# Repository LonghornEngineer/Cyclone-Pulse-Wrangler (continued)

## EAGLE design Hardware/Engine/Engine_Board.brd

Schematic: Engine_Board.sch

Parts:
3.3V: TEST_POINT_SINGLE_KEYSTONE_5115-5119; KEYSTONE_5115-5119
3.3V_PWR: MF-LED-0805-RED; LED_0805; MPN MF-LED-0805-RED
5V, 12V: TEST_POINT_SINGLE_KEYSTONE_5115-5119; KEYSTONE_5115-5119; MPN 5115
C1, C2, C3, C4, C7, C8, C9, C11, C12, C25, C26, C31, C32, C33, C34, C35, C37, C38, C39, C40: 0.1uF; 0805
C5: 0.1uF; 0603
C6, C44, C45: 10uF; 1210
C10, C13, C29, C30: 4.7uF; 1210; MPN GRJ32DC72A475KE11L
C14: 1uf; 0805; MPN C0805C105K5RACTU
C15: 1000uF; 10MM_CAP_SMD; MPN UWZ1A102MCL1GS
C16, C23: 0.1uF; 0805; MPN MF-CAP-0805-0.1uF
C17: 10uF; 1206; MPN MF-CAP-1206-10uF
C18: 1000uF; 12.5MM_CAP_PTH; MPN UBW1H102MHD
C19: 220uF; 10MM_CAP_SMD; MPN UWZ1H221MCL1GS
C22: 10uF; 1210; MPN MF-CAP-1206-10uF
C24: 47uF; 6.3MM_CAP_SMD; MPN UWJ1C470MCL1GB
C27: 0.01uF; 0805; MPN C0805C103K5RACTU
C28: 180uF; 8MM_CAP_SMD; MPN 16SVP180M
C36: 4.7uF; 0805
C41, C42, C43: .1uF; 0603
D2: VS-12CWQ10FN-M3; D-PAK(TO-252AA); MPN VS-12CWQ10FN-M3
D3: VB20100S-E3/8W; D2PAK(TO-263AB)
D7, D8, D9, D10: NUP2105LT1G; SOT-23
DISP1: 61201621621; CU40045-UW1J
FID1, FID2: FIDUCIAL_0.5MM
GND: TEST_POINT_SINGLE_KEYSTONE_5115-5119; KEYSTONE_5115-5119; MPN 5115
J1, J2, J3, J4, J5: CON_01X02_1546215-2; 1546215-2
J6: 3PCV-03-006; MPN 3PCV-03-006
L3: 6.8uH; IHLP-5050; MPN IHLP5050CEER6R8M01
PROP_TC: TC2030-NL; TC2030
PROP_UART: CON_01X06_2.54MM_PIN_HEADER; 2.54MM_01X06_PIN_HEADER
R1, R9, R10, R15, R16, R17: 10K; 0805
R2: 470K; 0603; MPN MF-RES-0603-470K
R3, R4, R5, R6, R7, R8, R14, R18: 120; 0603
R11: 330; 0603; MPN MF-RES-0603-330
R12, R13: 10K; 0603
R19, R20, R21, R22, R23, R24, R25, R26, R27, R28, R29, R30, R31, R32, R33, R34, R35, R36, R37, R38, R39, R40, R41, R42, R43, R44, R45: RESISTOR_0603; R0603
RELAYS: CON_01X10_1-282834-0; 1-282834-0
SW1, SW2, SW3: MF-SW-TACT-4.2MM; TACT4.2MM
SWITCHS: CON_01X10_1-282834-0; 1-282834-0
SW_D: CON_01X02_1546215-2; 1546215-2
SW_S: CON_01X02_1546215-2; 1546215-2
SW_U: CON_01X02_1546215-2; 1546215-2
TVS1: V18AUMLA2220H; 2220
U1: P8X32A-Q44; LQFP44
U2, U3, U8, U12, U13, U15, U17, U18, U19, U20, U21, U22, U23, U24, U25, U26: G3VM-61GR2(TR05); G3VM-61GR2
U4, U9, U10, U11: MAX31855KASA+; MAX31855_SO-8
U5: LM22678TJ-5.0/NOPB; LM22678_TO-263-EP-7; MPN LM22678TJ-5.0/NOPB
U6: ADP3338AKCZ-3.3-RL; ADP3338_SOT-223-3; MPN ADP3338AKCZ-3.3-RL
U7: CAT24C512WI-GT3; SOIC-8_W
U14: CD74HC595M96; CD74HC595_SOIC-16
U16: CD74HC165M96; CD74HC165_SOIC-16
U27: FXOS8700CQR1
U28: ACPL-C870-000E; ACPL-C87_SSO-8
U29: MAX11613EUA+; MAX11613_UMAX-8
U30: TPS7B6933QDCYRQ1; SOT-23-5
U$1: LHE_FRAME
U$35: JEEP_LOGO_SILK_MEDIUM; JEEP_SILK_MEDIUM
U$42: LHE_LOGOLHE_LOGO; LHE_LOGO
X1: ABMM-6.000MHZ-B2-T; 7MMX5MM

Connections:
3.3V: 3.3V.P$1, C1.1, C2.1, C3.1, C4.1, C7.1, C8.1, C9.1, C11.1, C22.1, C23.1, C24.POS, C25.1, C31.1, C32.1, C34.1, C36.1, C37.1, C38.1, C41.1, C43.1, R1.2, R9.1, R10.1, R11.1, R12.2, R13.2, R15.2, R16.2, R17.1, R28.P$2, R29.P$2, R30.P$2, R31.P$2, R32.P$2, R33.P$2, R34.P$2, R35.P$2, U1.8 (VDD), U1.18 (VDD), U1.30 (VDD), U1.40 (VDD), U4.4 (VCC), U6.2 (OUT), U6.PAD (OUT), U7.8 (VCC), U9.4 (VCC), U10.4 (VCC), U11.4 (VCC), U14.10 (MR), U14.16 (VCC), U16.16 (VCC), U27.P$1 (VDDIO), U27.P$14 (VDD), U28.P$8 (VDD2), U29.P$8 (VCC)
5V: 5V.P$1, C13.1, C15.POS, C16.1, C17.1, C28.POS, L3.1, U5.P$6 (FB), U6.3 (IN)
5V_PWR: C6.1, DISP1.P$13 (VCC)
12V: 12V.P$1, C10.1, C14.1, C18.POS, C19.POS, C29.1, C30.1, D2.PAD-4 (CATHODE), R2.1, U5.P$2 (VIN)
12V_BATT: D2.1 (ANODE), D2.3 (ANODE), J6.1 (PIN1), TVS1.P$2
12V_BATT_ON: C44.1, U30.P$1 (VIN)
165_CLK: U1.14 (P13), U16.2 (CLK)
165_DATA: U1.12 (P11), U16.9 (QH)
165_LOAD: U1.13 (P12), U16.1 (LAT)
595_CLK: U1.19 (P16), U14.11 (SHCP)
595_DATA: U1.15 (P14), U14.14 (DS)
595_LAT: U1.16 (P15), U14.12 (STCP)
!RES!_PROP: C5.1, PROP_TC.P$6 (PIN6), PROP_UART.6
A0: R43.P$2, U29.P$1 (A_0)
A1: U29.P$2 (A_1)
A2: U29.P$3 (A_2)
A3: U29.P$4 (A_3)
CHASSIS_GND: C44.2, C45.2, R44.P$1, U2.P$3 (3), U3.P$3 (3), U8.P$3 (3), U12.P$3 (3), U13.P$3 (3), U15.P$3 (3), U17.P$3 (3), U18.P$3 (3), U19.P$2 (CATHODE), U20.P$2 (CATHODE), U21.P$2 (CATHODE), U22.P$2 (CATHODE), U23.P$2 (CATHODE), U24.P$2 (CATHODE), U25.P$2 (CATHODE), U26.P$2 (CATHODE), U28.P$3 (SHDN), U28.P$4 (GND1), U30.P$3 (GND/ADJ), U30.P$4 (GND/ADJ)
D4: DISP1.P$3 (D4), R6.2
D5: DISP1.P$4 (D5), R5.2
D6: DISP1.P$1 (D6), R4.2
D7: DISP1.P$2 (D7), R3.2
DOME_PWR: J6.3 (PIN3)
E1: DISP1.P$10 (E1), R8.2
E2: DISP1.P$16 (E2), R7.2
EXT_5V: C45.1, U28.P$1 (VDD1), U30.P$5 (VOUT)
GND: 3.3V_PWR.CATHODE, C1.2, C2.2, C3.2, C4.2, C6.2, C7.2, C8.2, C9.2, C10.2, C11.2, C13.2, C14.2, C15.NEG, C16.2, C17.2, C18.NEG, C19.NEG, C22.2, C23.2, C24.NEG, C25.2, C26.2, C28.NEG, C29.2, C30.2, C31.2, C32.2, C34.2, C36.2, C37.2, C38.2, C40.2, C41.2, C42.2, C43.2, D3.A (ANODE), D7.3, D8.3, D9.3, D10.3, DISP1.P$5 (D2), DISP1.P$6 (D3), DISP1.P$7 (D0), DISP1.P$8 (D1), DISP1.P$14 (GND), GND.P$1, J6.2 (PIN2), PROP_TC.P$5 (PIN5), PROP_UART.1, SW1.P$4, SW2.P$4, SW3.P$4, SW_D.P$2 (PIN2), SW_S.P$2 (PIN2), SW_U.P$2 (PIN2), TVS1.P$1, U1.5 (VSS), U1.6 (BOE'), U1.17 (VSS), U1.27 (VSS), U1.39 (VSS), U2.P$2 (CATHODE), U3.P$2 (CATHODE), U4.1 (GND), U5.P$4 (GND), U5.PAD (GND), U6.1 (GND), U7.2 (A1), U7.3 (A2), U7.4 (GND), U7.7 (WP), U8.P$2 (CATHODE), U9.1 (GND), U10.1 (GND), U11.1 (GND), U12.P$2 (CATHODE), U13.P$2 (CATHODE), U14.8 (GND), U14.13 (OE), U15.P$2 (CATHODE), U16.8 (GND), U16.15 (C_INH), U17.P$2 (CATHODE), U18.P$2 (CATHODE), U19.P$3 (3), U20.P$3 (3), U21.P$3 (3), U22.P$3 (3), U23.P$3 (3), U24.P$3 (3), U25.P$3 (3), U26.P$3 (3), U27.P$3 (GND), U27.P$5 (GND), U27.P$7 (SA0/MISO), U27.P$10 (SA1/CS_B), U27.P$12 (GND), U27.P$13 (GND), U27.P$16 (RST), U28.P$5 (GND2), U28.P$6 (VOUT-), U29.P$7 (GND), X1.P$2 (GND), X1.P$4 (GND)
IN_OPTO_1: R29.P$1, U16.12 (D1), U20.P$4 (4)
IN_OPTO_2: R30.P$1, U16.13 (D2), U21.P$4 (4)
IN_OPTO_3: R31.P$1, U16.14 (D3), U22.P$4 (4)
IN_OPTO_4: R32.P$1, U16.3 (D4), U23.P$4 (4)
IN_OPTO_5: R33.P$1, U16.4 (D5), U24.P$4 (4)
IN_OPTO_6: R34.P$1, U16.5 (D6), U25.P$4 (4)
IN_OPTO_7: R35.P$1, U16.6 (D7), U26.P$4 (4)
unnamed: R28.P$1, U16.11 (D0), U19.P$4 (4)
unnamed: C27.1, U5.P$3 (BOOT)
unnamed: R27.P$1, U19.P$1 (ANODE)
unnamed: R36.P$1, U20.P$1 (ANODE)
unnamed: C27.2, D3.C (CATHODE), L3.2, U5.P$1 (SW)
unnamed: R37.P$1, U21.P$1 (ANODE)
unnamed: C26.1, U27.P$2 (BYP)
unnamed: C40.1, U27.P$8 (CRST)
unnamed: 3.3V_PWR.ANODE, R11.2
unnamed: R38.P$1, U22.P$1 (ANODE)
unnamed: R19.P$2, U2.P$1 (ANODE)
unnamed: R20.P$2, U3.P$1 (ANODE)
unnamed: R21.P$2, U8.P$1 (ANODE)
unnamed: R22.P$2, U12.P$1 (ANODE)
unnamed: R23.P$2, U13.P$1 (ANODE)
unnamed: R24.P$2, U15.P$1 (ANODE)
unnamed: R25.P$2, U17.P$1 (ANODE)
unnamed: R26.P$2, U18.P$1 (ANODE)
unnamed: R39.P$1, U23.P$1 (ANODE)
unnamed: R40.P$1, U24.P$1 (ANODE)
unnamed: R41.P$1, U25.P$1 (ANODE)
unnamed: R42.P$1, U26.P$1 (ANODE)
unnamed: R27.P$2, SWITCHS.P$1 (1)
unnamed: R36.P$2, SWITCHS.P$2 (2)
unnamed: R37.P$2, SWITCHS.P$3 (3)
unnamed: R38.P$2, SWITCHS.P$4 (4)
unnamed: R39.P$2, SWITCHS.P$5 (5)
unnamed: R40.P$2, SWITCHS.P$6 (6)
unnamed: R41.P$2, SWITCHS.P$7 (7)
unnamed: R42.P$2, SWITCHS.P$8 (8)
unnamed: R2.2, U5.P$7 (EN)
unnamed: C42.1, R43.P$1, U28.P$7 (VOUT+)
unnamed: R44.P$2, R45.P$2, U28.P$2 (VIN)
unnamed: J5.P$1 (PIN1), R45.P$1
OUT_0: R19.P$1, U14.15 (Q0)
OUT_1: R20.P$1, U14.1 (Q1)
OUT_2: R21.P$1, U14.2 (Q2)
OUT_3: R22.P$1, U14.3 (Q3)
OUT_4: R23.P$1, U14.4 (Q4)
OUT_5: R24.P$1, U14.5 (Q5)
OUT_6: R25.P$1, U14.6 (Q6)
OUT_7: R26.P$1, U14.7 (Q7)
P0: U1.41 (P0)
P17: U1.20 (P17)
P18: U1.21 (P18)
PROP_D4: R6.1, U1.44 (P3)
PROP_D5: R5.1, U1.1 (P4)
PROP_D6: R4.1, U1.42 (P1)
PROP_D7: R3.1, U1.43 (P2)
PROP_E1: R8.1, U1.2 (P5)
PROP_E2: R7.1, U1.9 (P8)
PROP_R/W: R14.1, U1.3 (P6)
PROP_RES: C5.2, R1.1, U1.7 (RES')
PROP_RS: R18.1, U1.4 (P7)
R/W: DISP1.P$9 (R/W), R14.2
RLY_0: RELAYS.P$1 (1), U2.P$4 (4)
RLY_1: RELAYS.P$2 (2), U3.P$4 (4)
RLY_2: RELAYS.P$3 (3), U8.P$4 (4)
RLY_3: RELAYS.P$4 (4), U12.P$4 (4)
RLY_4: RELAYS.P$5 (5), U13.P$4 (4)
RLY_5: RELAYS.P$6 (6), U15.P$4 (4)
RLY_6: RELAYS.P$7 (7), U17.P$4 (4)
RLY_7: RELAYS.P$8 (8), U18.P$4 (4)
RS: DISP1.P$12 (RS), R18.2
RX_PROP: PROP_TC.P$4 (PIN4), PROP_UART.4, U1.38 (P31)
SCL: R15.1, U1.35 (P28), U7.6 (SCL)
SCL_1: R12.1, U1.11 (P10), U27.P$4 (SCL/SCKL), U29.P$5 (SCL)
SDA: R16.1, U1.36 (P29), U7.5 (SDA)
SDA_1: R13.1, U1.10 (P9), U27.P$6 (SDA/MOSI), U29.P$6 (SDA)
SW_D: R9.2, SW3.P$1, SW_D.P$1 (PIN1), U1.22 (P19)
SW_S: R10.2, SW2.P$1, SW_S.P$1 (PIN1), U1.23 (P20)
SW_U: R17.2, SW1.P$1, SW_U.P$1 (PIN1), U1.24 (P21)
T+_0: C33.1, D8.1, J1.P$1 (PIN1), U9.3 (T+)
T+_1: C35.1, D9.1, J2.P$1 (PIN1), U10.3 (T+)
T+_2: C39.1, D7.1, J3.P$1 (PIN1), U11.3 (T+)
T+_3: C12.1, D10.1, J4.P$1 (PIN1), U4.3 (T+)
T-_0: C33.2, D8.2, J1.P$2 (PIN2), U9.2 (T-)
T-_1: C35.2, D9.2, J2.P$2 (PIN2), U10.2 (T-)
T-_2: C39.2, D7.2, J3.P$2 (PIN2), U11.2 (T-)
T-_3: C12.2, D10.2, J4.P$2 (PIN2), U4.2 (T-)
TC_CS_0: U1.25 (P22), U9.6 (!CS)
TC_CS_1: U1.26 (P23), U10.6 (!CS)
TC_CS_2: U1.31 (P24), U11.6 (!CS)
TC_CS_3: U1.32 (P25), U4.6 (!CS)
TC_SCK: U1.34 (P27), U4.5 (SCK), U9.5 (SCK), U10.5 (SCK), U11.5 (SCK)
TC_SO: U1.33 (P26), U4.7 (SO), U9.7 (SO), U10.7 (SO), U11.7 (SO)
TX_PROP: PROP_TC.P$3 (PIN3), PROP_UART.5, U1.37 (P30)
X0: U1.29 (X0), X1.P$1 (X0)
X1: U1.28 (X1), X1.P$3 (X1)

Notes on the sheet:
POWER INPUT
5V POWER SUPPLY

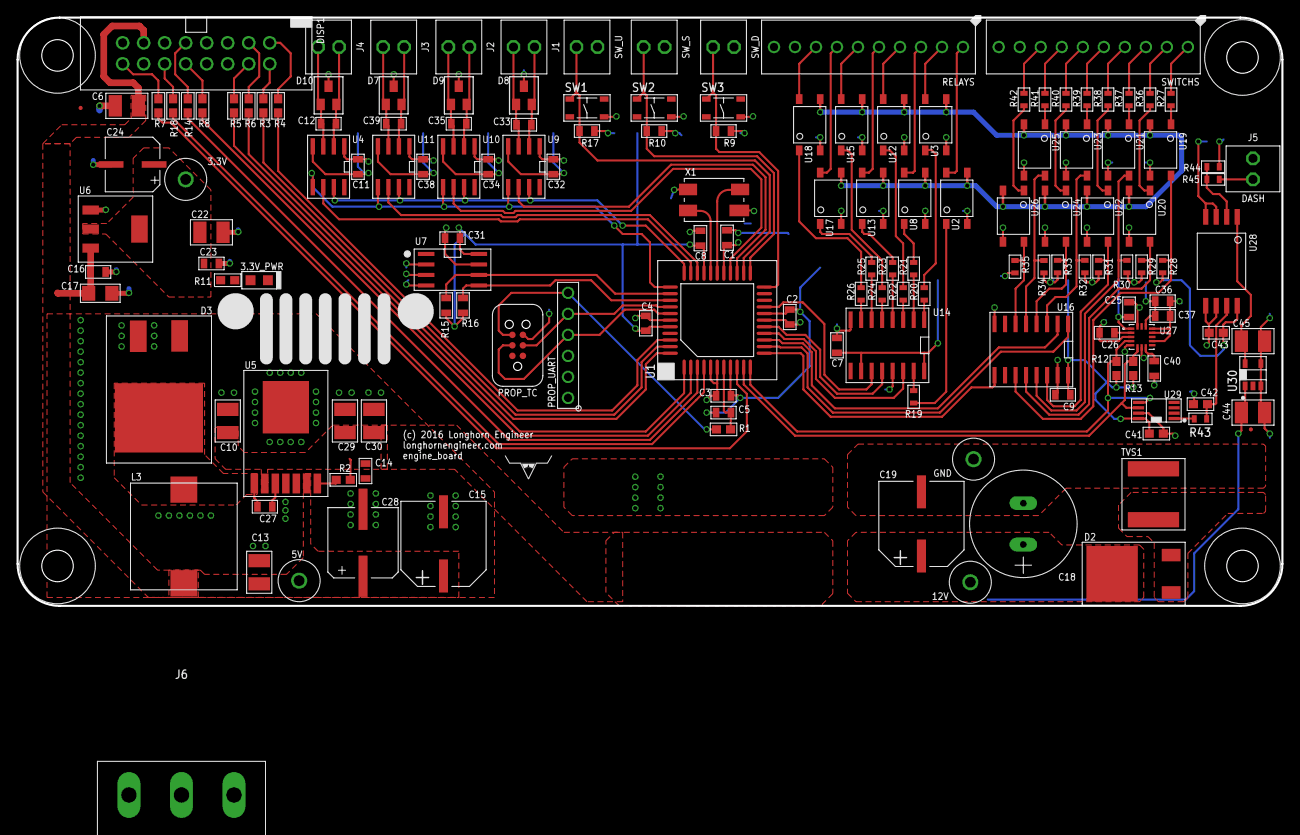
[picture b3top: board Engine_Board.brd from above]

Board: 2 copper layers, 152.9 x 71.1 mm, 158 parts (0 on the bottom side), 116 nets.

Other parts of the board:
U$31, U$32, U$33, U$34: MOUNT_HOLE_150MIL

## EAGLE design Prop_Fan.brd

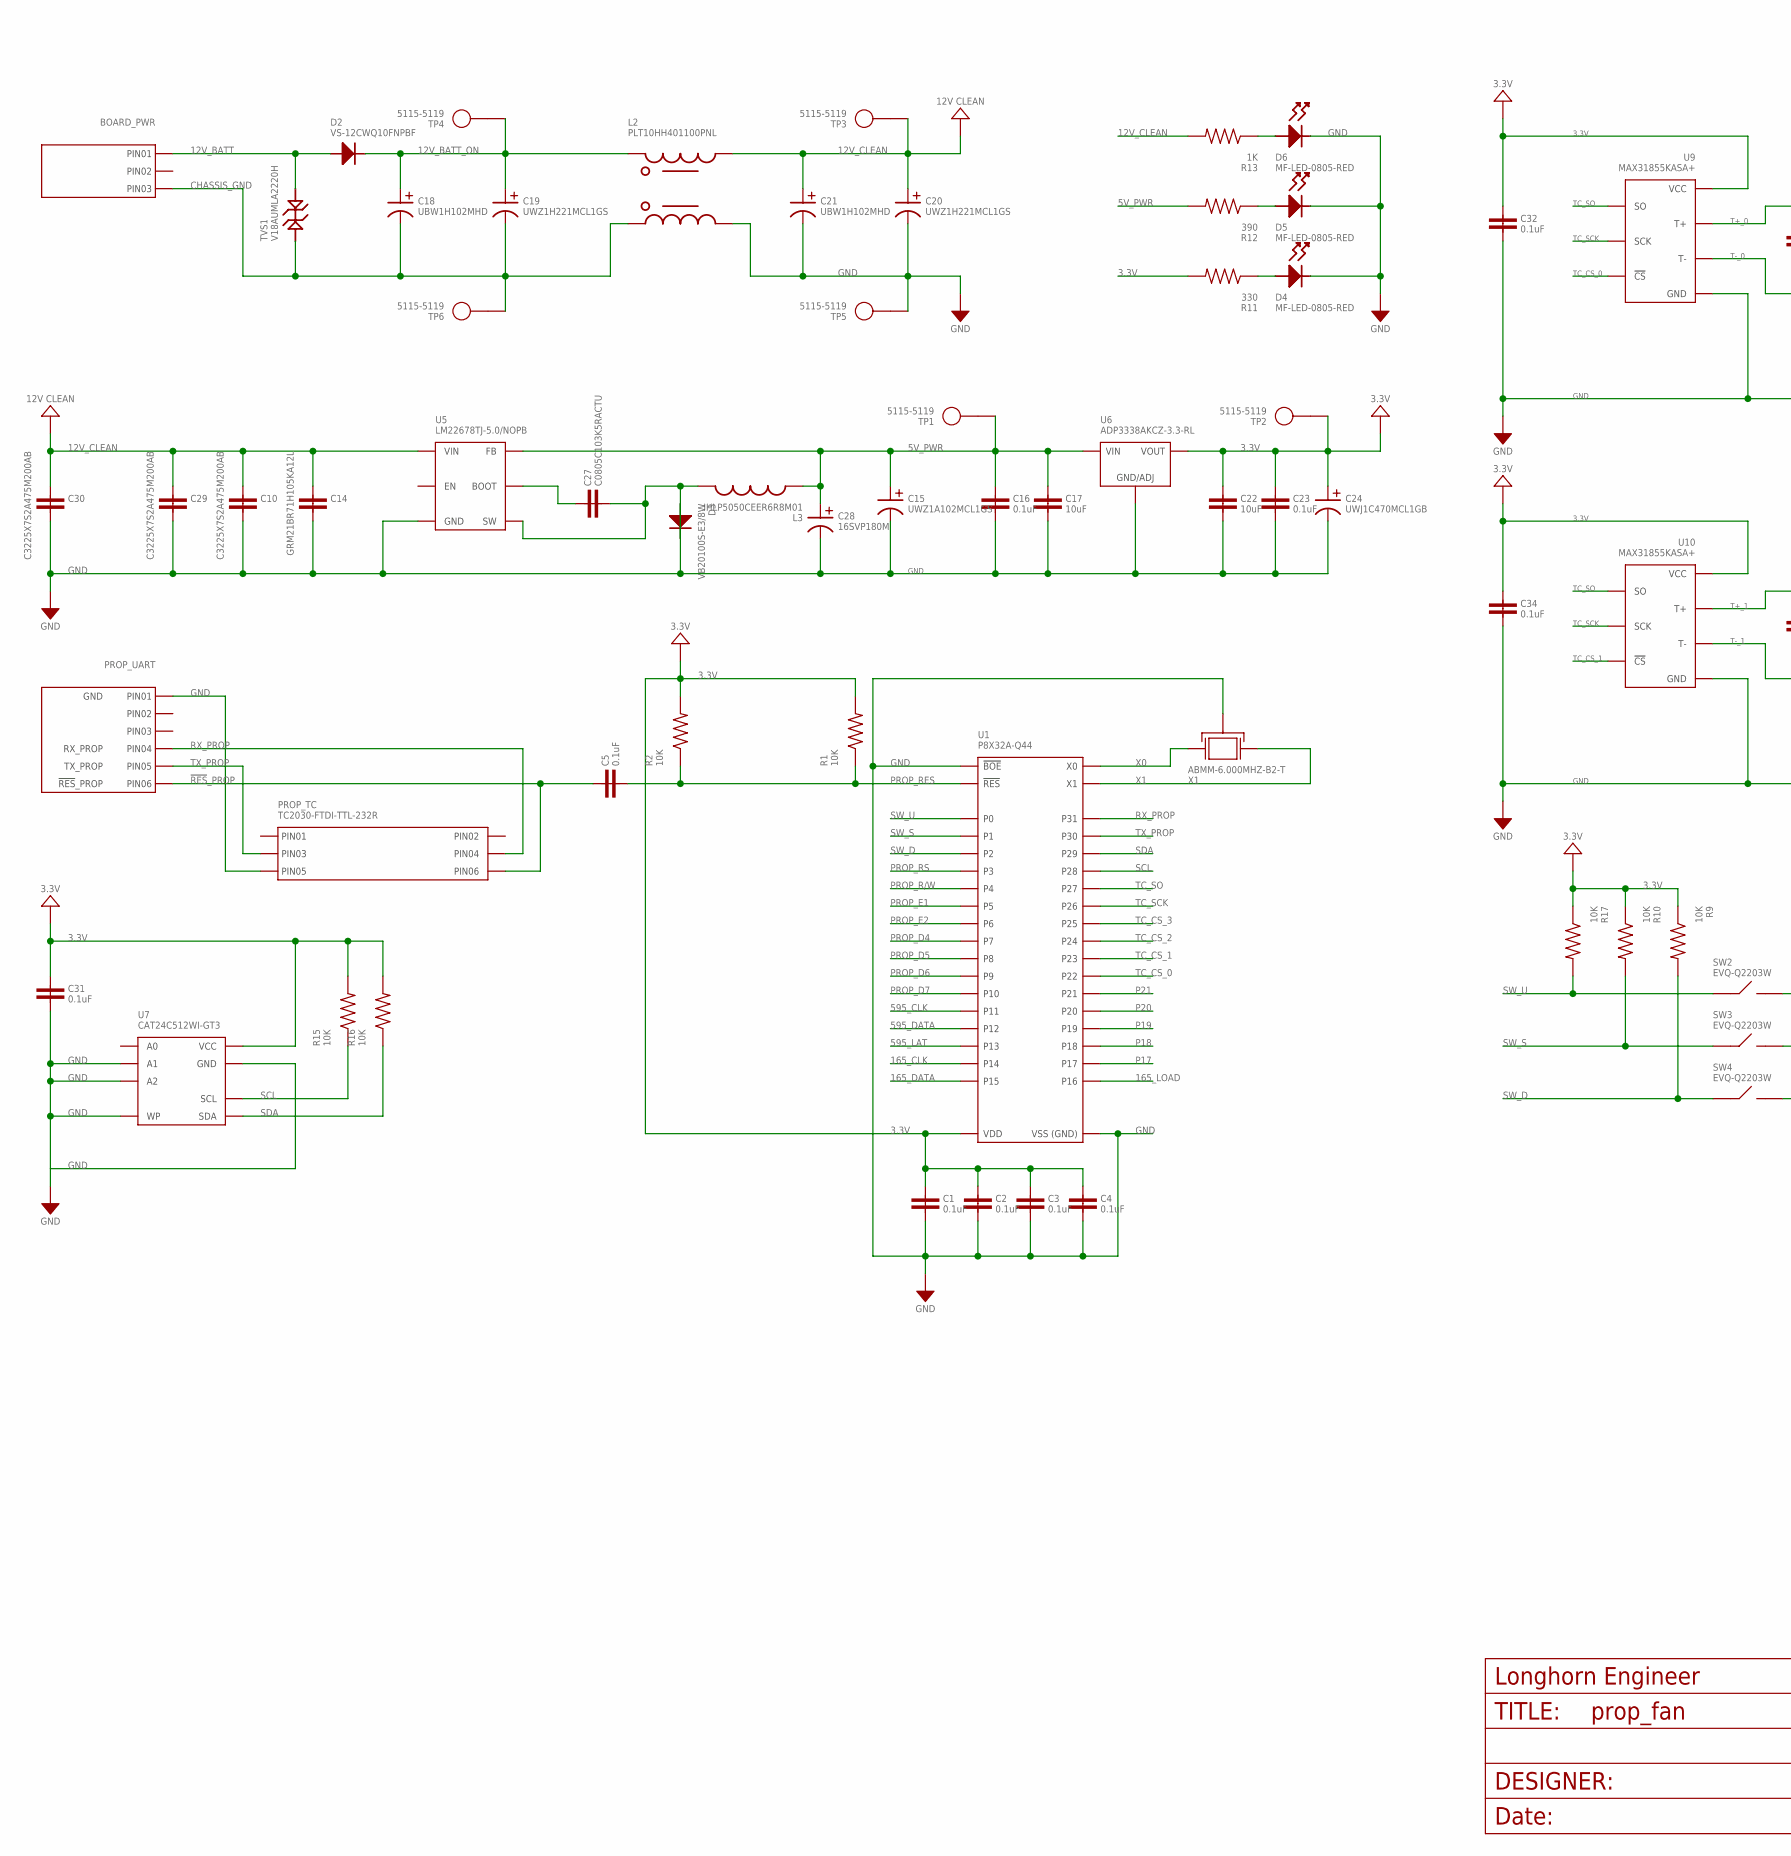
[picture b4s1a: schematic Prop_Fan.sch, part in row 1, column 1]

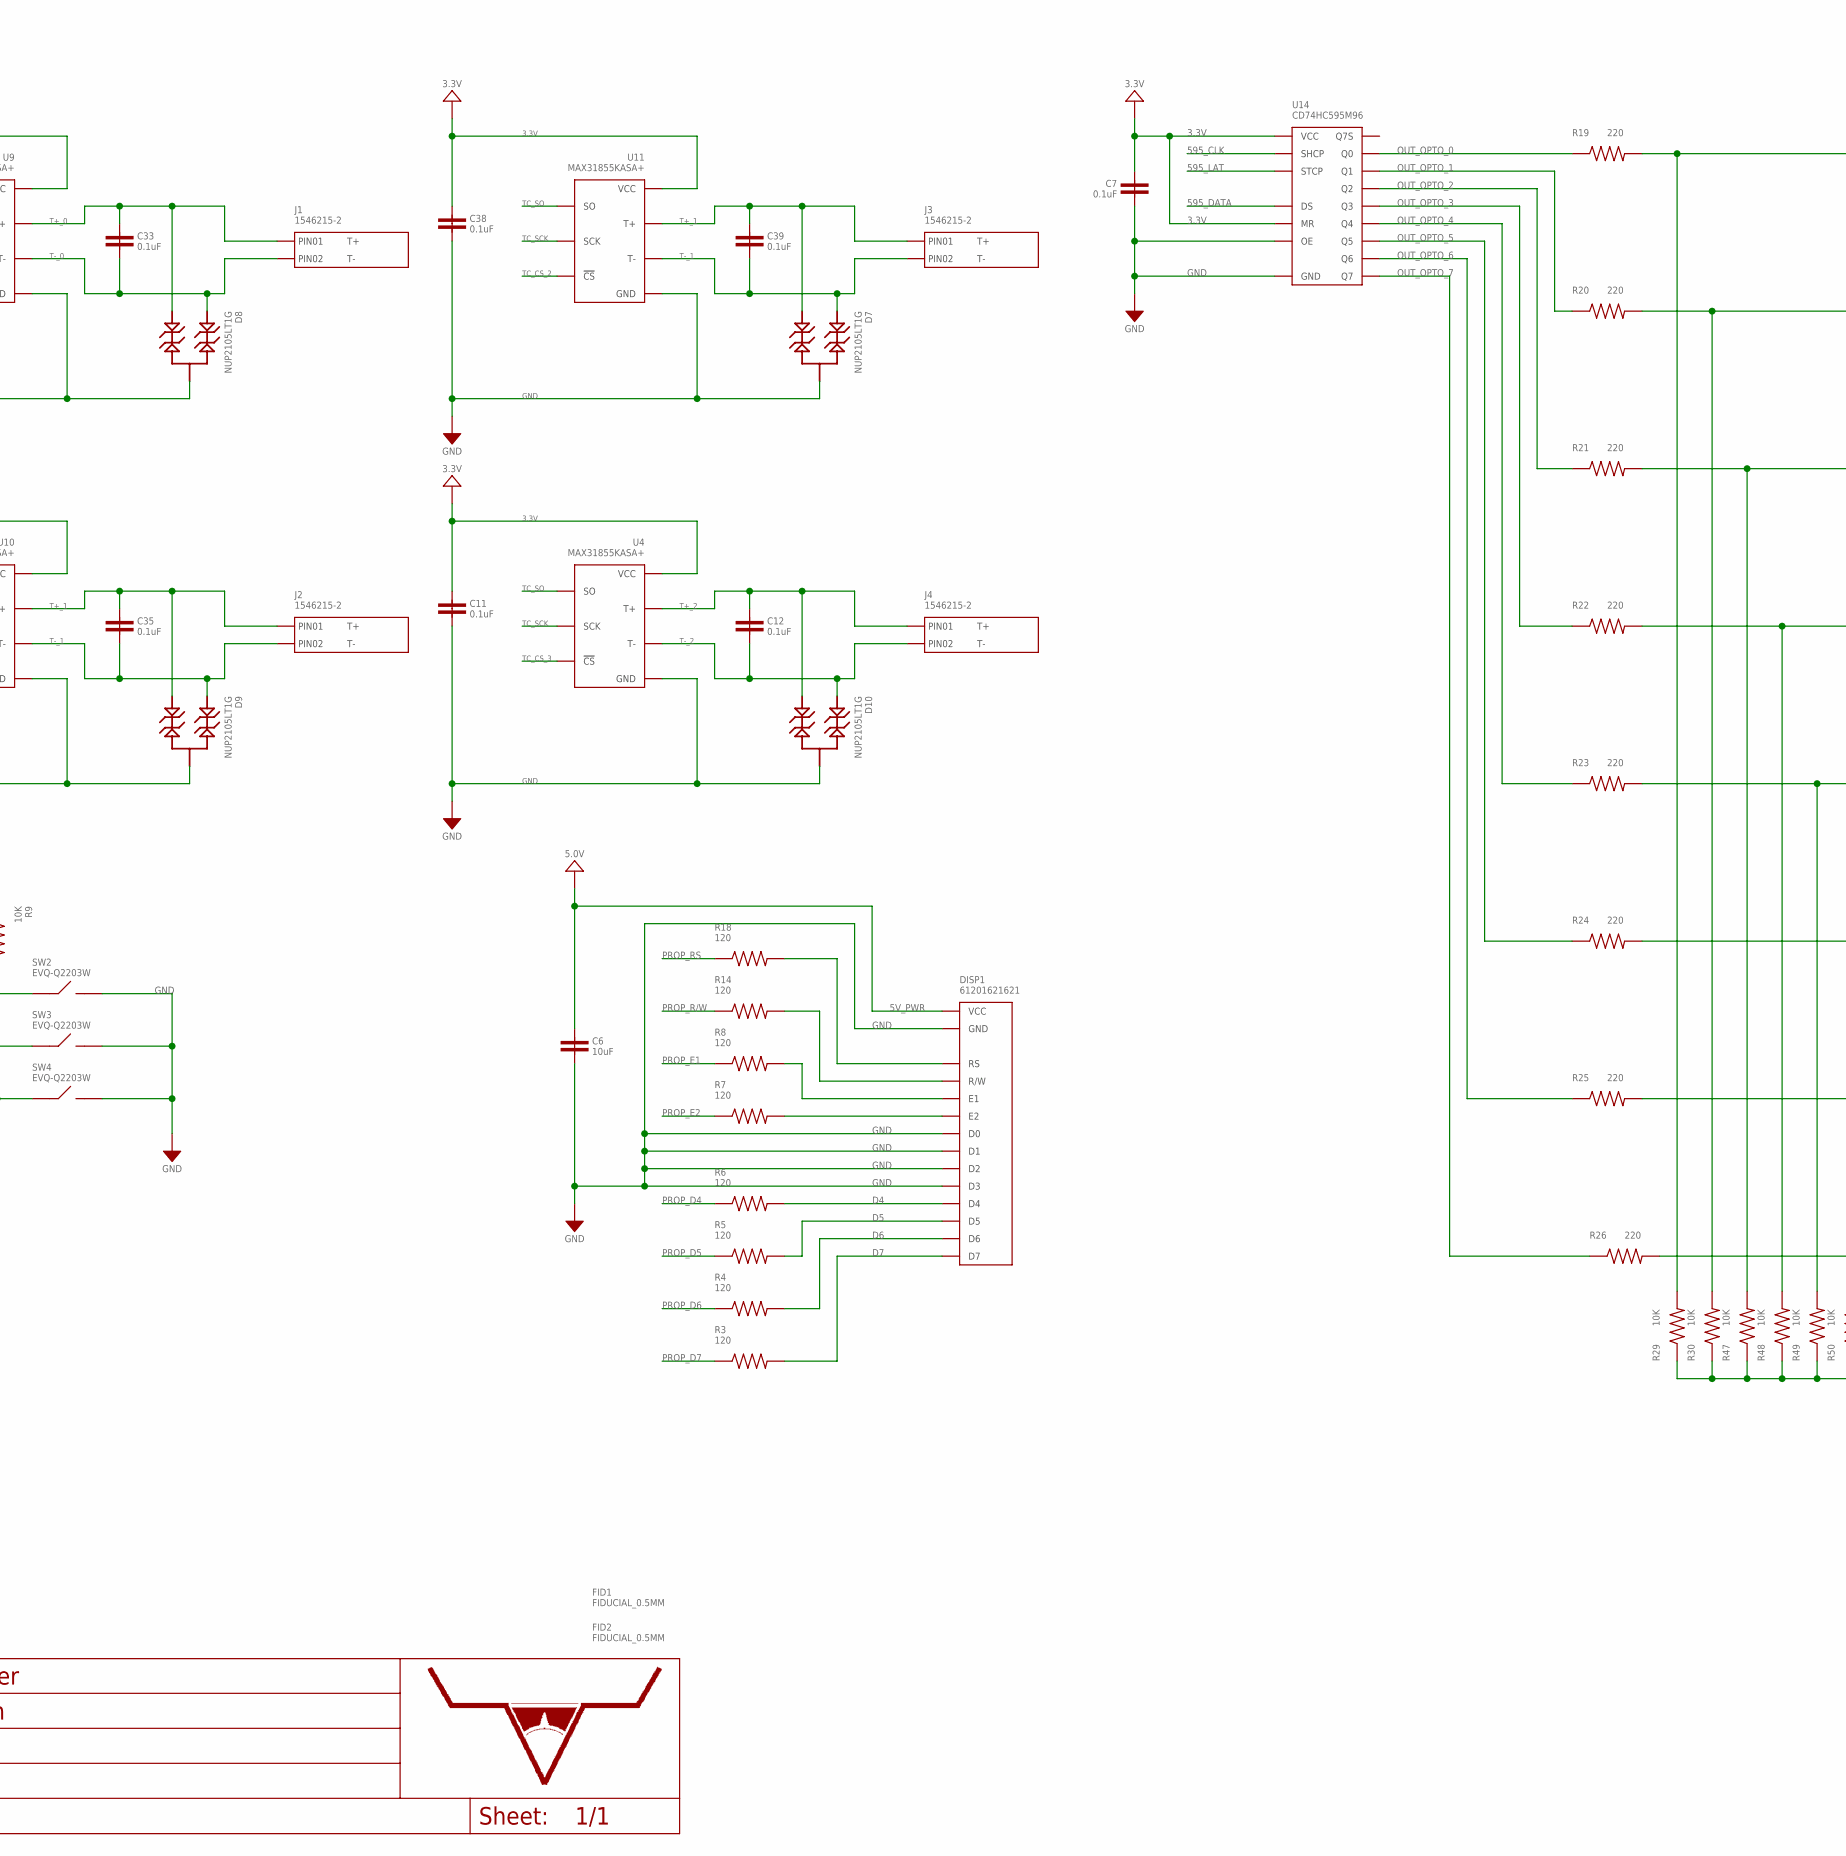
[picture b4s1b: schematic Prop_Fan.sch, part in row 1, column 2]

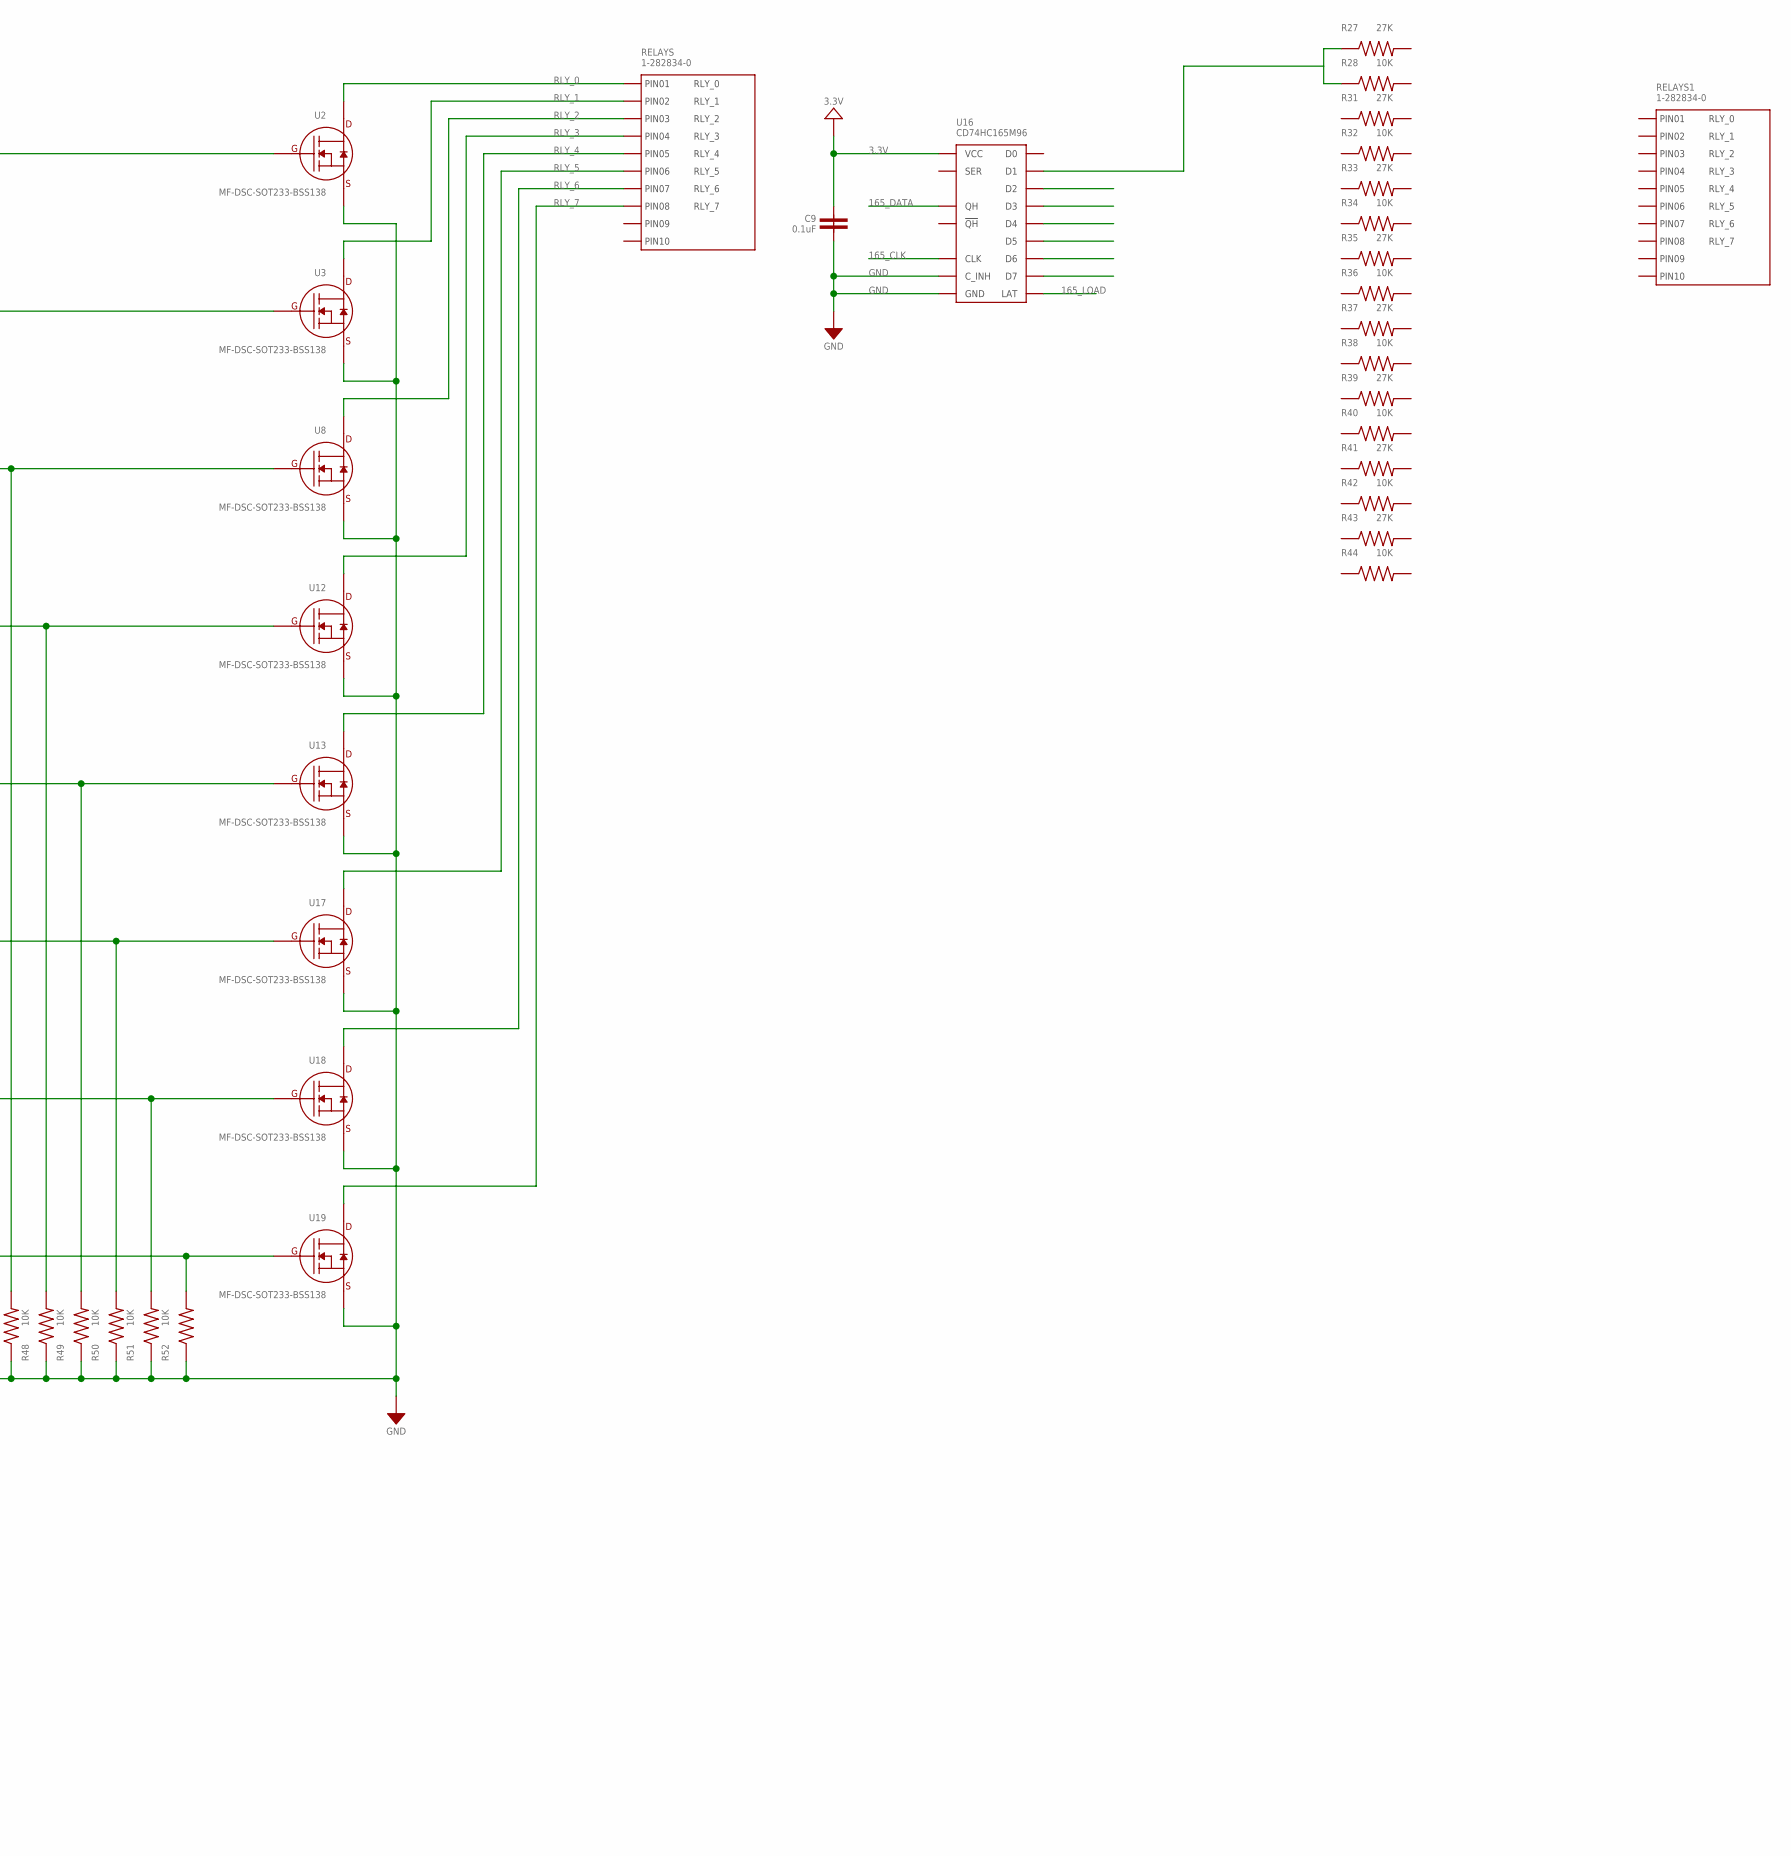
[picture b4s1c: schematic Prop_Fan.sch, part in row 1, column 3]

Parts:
BOARD_PWR: CON_01X03_640454-3; 640454-3
C1, C2, C3, C4, C5, C7, C9, C11, C12, C16, C23, C31, C32, C33, C34, C35, C38, C39: 0.1uF; 0805
C6, C17, C22: 10uF; 0805
C10, C29, C30: C3225X7S2A475M200AB; 1210
C14: GRM21BR71H105KA12L; 0805
C15: UWZ1A102MCL1GS; 10MM_CAP_SMD
C18, C21: UBW1H102MHD; 12.5MM_CAP_PTH
C19, C20: UWZ1H221MCL1GS; 10MM_CAP_SMD
C24: UWJ1C470MCL1GB; 6.3MM_CAP_SMD
C27: C0805C103K5RACTU; 0805
C28: 16SVP180M; 8MM_CAP_SMD
D2: VS-12CWQ10FNPBF; D-PAK(TO-252AA)
D3: VB20100S-E3/8W; D2PAK(TO-263AB)
D4, D5, D6: MF-LED-0805-RED; LED_0805
D7, D8, D9, D10: NUP2105LT1G; SOT-23
DISP1: 61201621621; CU40045-UW1J
FID1, FID2: FIDUCIAL_0.5MM
J1, J2, J3, J4: 1546215-2
L2: PLT10HH401100PNL; PLT10H
L3: IHLP5050CEER6R8M01; IHLP-5050
PROP_TC: TC2030-FTDI-TTL-232R; TC2030
PROP_UART: CON_01X06_2.54MM_PIN_HEADER; 2.54MM_01X06_PIN_HEADER
R1, R2, R9, R10, R15, R16, R17: 10K; 0805
R3, R4, R5, R6, R7, R8, R14, R18: 120; 0805
R11: 330; 0805
R12: 390; 0805
R13: 1K; 0805
R19, R20, R21, R22, R23, R24, R25, R26: 220; R0603
R27, R31, R33, R35, R37, R39, R41, R43: 27K; R0603
R28, R29, R30, R32, R34, R36, R38, R40, R42, R44, R47, R48, R49, R50, R51, R52: 10K; R0603
RELAYS, RELAYS1: 1-282834-0
SW2, SW3, SW4: EVQ-Q2203W
TP1, TP2, TP3, TP4, TP5, TP6: 5115-5119; KEYSTONE_5115-5119
TVS1: V18AUMLA2220H; 2220
U1: P8X32A-Q44; LQFP44
U2, U3, U8, U12, U13, U17, U18, U19: MF-DSC-SOT233-BSS138; SOT-23-3
U4, U9, U10, U11: MAX31855KASA+; MAX31855_SO-8
U5: LM22678TJ-5.0/NOPB; LM22678_TO-263-EP-7
U6: ADP3338AKCZ-3.3-RL; ADP3338_SOT-223-3
U7: CAT24C512WI-GT3; SOIC-8_W
U14: CD74HC595M96; CD74HC595_SOIC-16
U16: CD74HC165M96; CD74HC165_SOIC-16
U$1: LHE_FRAME
X1: ABMM-6.000MHZ-B2-T; 7MMX5MM

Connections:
3.3V: C1.1, C2.1, C3.1, C4.1, C7.1, C9.1, C11.1, C22.1, C23.1, C24.POS, C31.1, C32.1, C34.1, C38.1, R1.2, R2.2, R9.1, R10.1, R11.2, R15.2, R16.2, R17.1, TP2.P$1, U1.8 (VDD), U1.18 (VDD), U1.30 (VDD), U1.40 (VDD), U4.4 (VCC), U6.2 (OUT), U6.PAD (OUT), U7.8 (VCC), U9.4 (VCC), U10.4 (VCC), U11.4 (VCC), U14.10 (MR), U14.16 (VCC), U16.16 (VCC)
5V_PWR: C6.1, C15.POS, C16.1, C17.1, C28.POS, DISP1.P$14 (VCC), L3.1, R12.2, TP1.P$1, U5.P$6 (FB), U6.3 (IN)
12V_BATT: BOARD_PWR.P$1 (PIN1), D2.1 (ANODE), D2.3 (ANODE), TVS1.P$2
12V_BATT_ON: C18.POS, C19.POS, D2.PAD-4 (CATHODE), L2.1, TP4.P$1
12V_CLEAN: C10.1, C14.1, C20.POS, C21.POS, C29.1, C30.1, L2.2, R13.2, TP3.P$1, U5.P$2 (VIN)
165_CLK: U1.15 (P14), U16.2 (CLK)
165_DATA: U1.16 (P15), U16.9 (QH)
165_LOAD: U1.19 (P16), U16.1 (LAT)
595_CLK: U1.12 (P11), U14.11 (SHCP)
595_DATA: U1.13 (P12), U14.14 (DS)
595_LAT: U1.14 (P13), U14.12 (STCP)
!RES!_PROP: C5.1, PROP_TC.P$6 (PIN6), PROP_UART.6
CHASSIS_GND: BOARD_PWR.P$3 (PIN3), C18.NEG, C19.NEG, L2.4, TP6.P$1, TVS1.P$1
D4: DISP1.P$4 (D4), R6.2
D5: DISP1.P$3 (D5), R5.2
D6: DISP1.P$2 (D6), R4.2
D7: DISP1.P$1 (D7), R3.2
E1: DISP1.P$9 (E1), R8.2
E2: DISP1.P$15 (E2), R7.2
GND: C1.2, C2.2, C3.2, C4.2, C6.2, C7.2, C9.2, C10.2, C11.2, C14.2, C15.NEG, C16.2, C17.2, C20.NEG, C21.NEG, C22.2, C23.2, C24.NEG, C28.NEG, C29.2, C30.2, C31.2, C32.2, C34.2, C38.2, D3.A (ANODE), D4.CATHODE, D5.CATHODE, D6.CATHODE, D7.3, D8.3, D9.3, D10.3, DISP1.P$5 (D3), DISP1.P$6 (D2), DISP1.P$7 (D1), DISP1.P$8 (D0), DISP1.P$13 (GND), L2.3, PROP_TC.P$5 (PIN5), PROP_UART.1, SW2.3 (B), SW2.4 (B), SW3.3 (B), SW3.4 (B), SW4.3 (B), SW4.4 (B), TP5.P$1, U1.5 (VSS), U1.6 (BOE'), U1.17 (VSS), U1.27 (VSS), U1.39 (VSS), U4.1 (GND), U5.P$4 (GND), U5.PAD (GND), U6.1 (GND), U7.2 (A1), U7.3 (A2), U7.4 (GND), U7.7 (WP), U9.1 (GND), U10.1 (GND), U11.1 (GND), U14.8 (GND), U14.13 (OE), U16.8 (GND), U16.15 (C_INH), X1.P$2 (GND), X1.P$4 (GND)
IN_OPTO_1: R27.P$1, R28.P$1, U16.12 (D1)
IN_OPTO_2: U16.13 (D2)
IN_OPTO_3: U16.14 (D3)
IN_OPTO_4: U16.3 (D4)
IN_OPTO_5: U16.4 (D5)
IN_OPTO_6: U16.5 (D6)
IN_OPTO_7: U16.6 (D7)
unnamed: C27.1, U5.P$3 (BOOT)
unnamed: C27.2, D3.C (CATHODE), L3.2, U5.P$1 (SW)
unnamed: D6.ANODE, R13.1
unnamed: D5.ANODE, R12.1
unnamed: D4.ANODE, R11.1
unnamed: R19.P$2, R29.P$2, U2.P$1 (GATE)
unnamed: R20.P$2, R30.P$2, U3.P$1 (GATE)
unnamed: R21.P$2, R47.P$2, U8.P$1 (GATE)
unnamed: R22.P$2, R48.P$2, U12.P$1 (GATE)
unnamed: R23.P$2, R49.P$2, U13.P$1 (GATE)
unnamed: R24.P$2, R50.P$2, U17.P$1 (GATE)
unnamed: R25.P$2, R51.P$2, U18.P$1 (GATE)
unnamed: R26.P$2, R52.P$2, U19.P$1 (GATE)
OUT_OPTO_0: R19.P$1, U14.15 (Q0)
OUT_OPTO_1: R20.P$1, U14.1 (Q1)
OUT_OPTO_2: R21.P$1, U14.2 (Q2)
OUT_OPTO_3: R22.P$1, U14.3 (Q3)
OUT_OPTO_4: R23.P$1, U14.4 (Q4)
OUT_OPTO_5: R24.P$1, U14.5 (Q5)
OUT_OPTO_6: R25.P$1, U14.6 (Q6)
OUT_OPTO_7: R26.P$1, U14.7 (Q7)
P17: U1.20 (P17)
P18: U1.21 (P18)
P19: U1.22 (P19)
P20: U1.23 (P20)
P21: U1.24 (P21)
P$1: R29.P$1, R30.P$1, R47.P$1, R48.P$1, R49.P$1, R50.P$1, R51.P$1, R52.P$1, U2.P$2 (SOURCE), U3.P$2 (SOURCE), U8.P$2 (SOURCE), U12.P$2 (SOURCE), U13.P$2 (SOURCE), U17.P$2 (SOURCE), U18.P$2 (SOURCE), U19.P$2 (SOURCE)
PROP_D4: R6.1, U1.4 (P7)
PROP_D5: R5.1, U1.9 (P8)
PROP_D6: R4.1, U1.10 (P9)
PROP_D7: R3.1, U1.11 (P10)
PROP_E1: R8.1, U1.2 (P5)
PROP_E2: R7.1, U1.3 (P6)
PROP_R/W: R14.1, U1.1 (P4)
PROP_RES: C5.2, R1.1, R2.1, U1.7 (RES')
PROP_RS: R18.1, U1.44 (P3)
R/W: DISP1.P$10 (R/W), R14.2
RLY_0: RELAYS.P$1 (1), U2.P$3 (DRAIN)
RLY_1: RELAYS.P$2 (2), U3.P$3 (DRAIN)
RLY_2: RELAYS.P$3 (3), U8.P$3 (DRAIN)
RLY_3: RELAYS.P$4 (4), U12.P$3 (DRAIN)
RLY_4: RELAYS.P$5 (5), U13.P$3 (DRAIN)
RLY_5: RELAYS.P$6 (6), U17.P$3 (DRAIN)
RLY_6: RELAYS.P$7 (7), U18.P$3 (DRAIN)
RLY_7: RELAYS.P$8 (8), U19.P$3 (DRAIN)
RS: DISP1.P$11 (RS), R18.2
RX_PROP: PROP_TC.P$4 (PIN4), PROP_UART.4, U1.38 (P31)
SCL: R15.1, U1.35 (P28), U7.6 (SCL)
SDA: R16.1, U1.36 (P29), U7.5 (SDA)
SW_D: R9.2, SW4.1 (A), SW4.2 (A), U1.43 (P2)
SW_S: R10.2, SW3.1 (A), SW3.2 (A), U1.42 (P1)
SW_U: R17.2, SW2.1 (A), SW2.2 (A), U1.41 (P0)
T+_0: C33.1, D8.2, J1.P$1 (PIN1), U9.3 (T+)
T+_1: C35.1, C39.1, D7.2, D9.2, J2.P$1 (PIN1), J3.P$1 (PIN1), U10.3 (T+), U11.3 (T+)
T+_2: C12.1, D10.2, J4.P$1 (PIN1), U4.3 (T+)
T-_0: C33.2, D8.1, J1.P$2 (PIN2), U9.2 (T-)
T-_1: C35.2, C39.2, D7.1, D9.1, J2.P$2 (PIN2), J3.P$2 (PIN2), U10.2 (T-), U11.2 (T-)
T-_2: C12.2, D10.1, J4.P$2 (PIN2), U4.2 (T-)
TC_CS_0: U1.25 (P22), U9.6 (!CS)
TC_CS_1: U1.26 (P23), U10.6 (!CS)
TC_CS_2: U1.31 (P24), U11.6 (!CS)
TC_CS_3: U1.32 (P25), U4.6 (!CS)
TC_SCK: U1.33 (P26), U4.5 (SCK), U9.5 (SCK), U10.5 (SCK), U11.5 (SCK)
TC_SO: U1.34 (P27), U4.7 (SO), U9.7 (SO), U10.7 (SO), U11.7 (SO)
TX_PROP: PROP_TC.P$3 (PIN3), PROP_UART.5, U1.37 (P30)
X0: U1.29 (X0), X1.P$1 (X0)
X1: U1.28 (X1), X1.P$3 (X1)

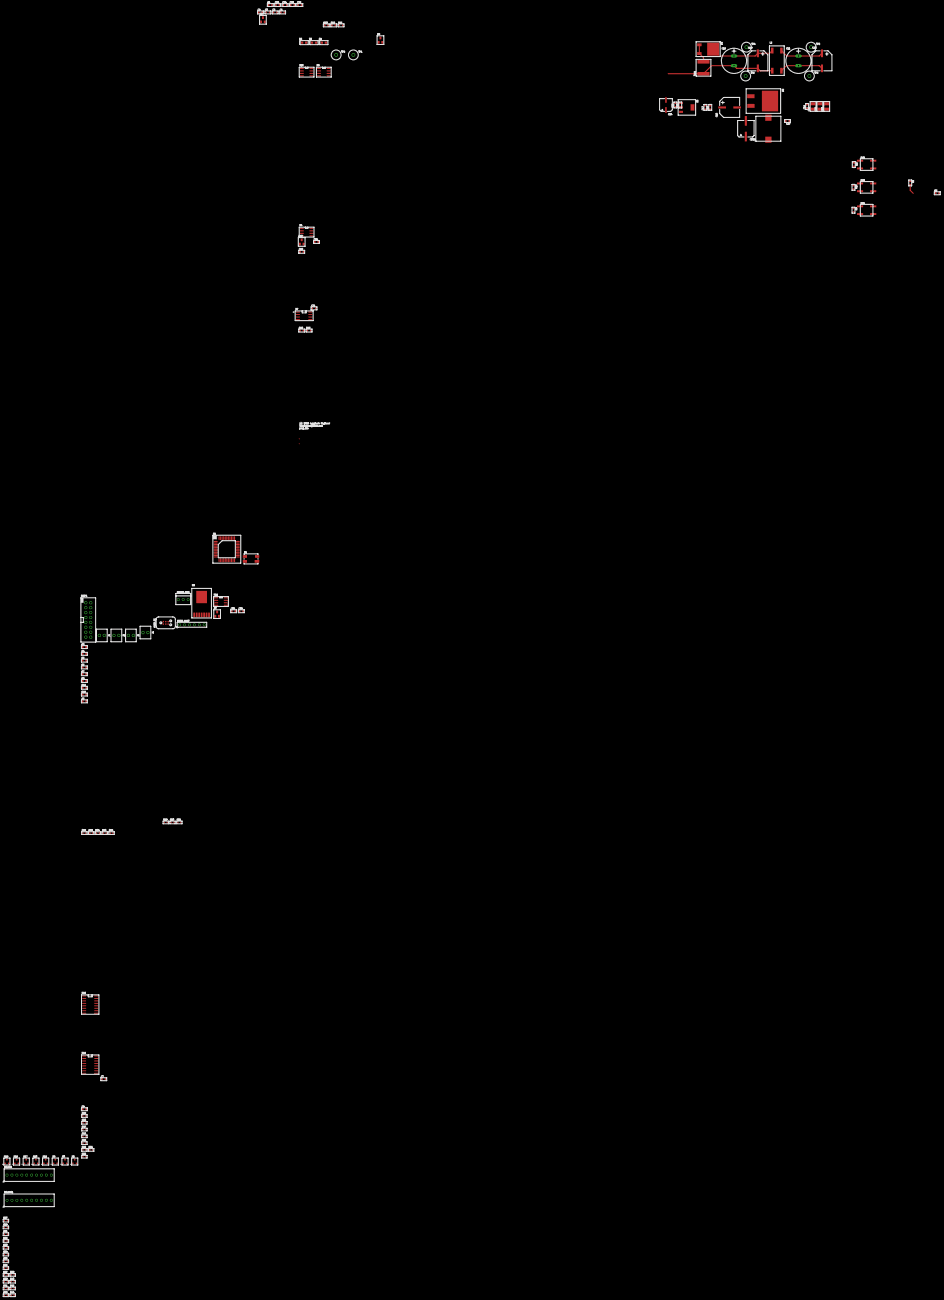
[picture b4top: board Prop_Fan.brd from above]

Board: 2 copper layers, 136 parts (0 on the bottom side), 83 nets.

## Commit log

2015-07-04 First push
2015-11-04 Change file name
2015-11-04 Need to add outputs.
2015-11-12 Starting Layout.
2015-11-13 Working on power layout.
2016-03-15 Need to add optos.
2016-04-19 Working on Schematic. Need to add optos. Display Added.
2016-04-19 Relay Control Hardware Complete.
2016-04-19 Working on Switch inputs. Voltage Dividers!
2016-04-20 Adding software! VFD Test code. Needs to be expanded.
2016-04-21 Added support for dual E lines for VFD.
2016-04-21 Fixed clear function bug.
2016-04-21 Fixed Initialize bug and wrote better demo code.
2016-04-21 Adding brightness control...
2016-04-22 brightness control working and in demo
2016-04-22 Added a clear to the demo.
2016-04-25 IMU E-compass added. Routing almost done.
    Need to add a way to look at the dome brightness.
2016-04-25 Corrected fids and added layout image.
2016-04-25 PROP Fan Rev 1 complete.
2016-04-26 Fixed a couple traces and added camfiles.
2016-04-26 New layout image.
2016-04-27 Fixed VFD connector. Was mirrored.
2016-05-19 Updated CU40045-UW1J footprint. Need to fix spacing.
2016-05-20 changed pinout for screen to match the hardware
2016-05-20 Removed timing
2016-05-21 Code almost there!
2016-05-22 FXO working correctly now.
2016-05-22 Using a different float32 function for more precision.
2017-08-28 Fixing up some software
2017-11-13 Working on new version
2021-07-27 new power input
2021-07-28 added LT8614
2021-08-25 cleaing up schematic more.
    8 analog inputs
    0-5V Analog in
    Thermistors
2021-09-15 added LTC2986HLX#PBF
2021-10-05 Control side of LTC2986HLX done.
2024-07-03 updating board files
2024-07-03 organizing hardware
2024-07-08 Initial schematic completed
2024-07-09 adding Display board and fixing problems with i2c diff pair
2024-07-12 Added push/pull drivers
2024-08-16 converting to Libre!
2024-08-18 working on the libre port
